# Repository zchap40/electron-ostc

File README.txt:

Acorn Electron Open Source Turbo Card
-------------------------------------

The Acorn Electron OSTC is a 'turbo card' that speeds up the Electron by partially 
mitigating the slow memory access that usually limits the 6502 CPU's performance. It 
acts similarly to ye olde turbo cards of days gone by, like the Slogger Turbo Driver, 
but is implemented using modern programmable logic and SRAM.

How it works
------------

Electrons are slow because of the ULA stealing RAM cycles to update the
display. When reading from the ROM the CPU works at 2MHz, but when accessing
RAM it runs at 1MHz in modes 4-6. In modes 0-3 the ULA stops the CPU clock
when drawing the display area, effectively throttling the 6502 down to 
around 0.5MHz.

Turbo cards are based on an interesting quirk; the ULA only needs to access
the upper 20K of system RAM for display purposes. The lower 12K is contended
between the ULA and CPU purely to simplify the Electron's design.

The trick is to stop the ULA from contending the lower 12K. We do this by
adding some new memory dedicated to the CPU, in this case a 32K SRAM chip.
All reads and writes to the 0-12K area are redirected to the SRAM chip - old
turbo cards handled the first 8K only to simplify the required logic, but here
we do all 12K. The 6502's databus is passed through the CPLD chip, which sets
it to high impedance when the SRAM is being accessed, effectively preventing
the Elk's on-board DRAM from causing bus contention.

That's great, but we're still not going any faster. The ULA is still throttling
the CPU clock, even when we're now accessing that lovely fast SRAM chip and not
the grotty contended motherboard DRAM.

The solution is to run the CPU's A15, A14 and RW lines through the CPLD. When
the CPU accesses the SRAM chip the CPLD pulls all of those lines high on the
ULA side, fooling it into thinking we are reading from the ROM - the the ULA
duly accelerates the CPU to 2MHz. The actual data read from the ROM never
reaches the CPU as the CPLD acts as a bus isolator at this point, cutting the CPU
and SRAM off from the motherboard.

One major difference between the older turbos and the OSTC is how 
disabling the board is handled. Other boards required a reboot after toggling
the board state. 

The OSTC never actually disables, the switch just returns the CPU to
normal speed. R/W operations are still processed by the SRAM chip, not DRAM.

This has the big advantage that SRAM contents is always up to date and turbo
speed can be toggled without a reboot. Downside is the very few games that try
to locate the display < 12K won't run.

Versions
--------

The OSTC was originally designed and developed by G. Colville (ramtop-retro).
OSTC_v1 can be downloaded from ramtop-retro/ostc.

Here we present a more compact version of the PCB, with an almost identical circuit,
filed here as OSTC_v2. The Electron is not just an elegant looking machine from
the exterior, but in my opinion, is also of elegant design on the inside too. I wanted
a version of the OSTC that matched the aesthetic of the Electron's motherboard without
being unnecessarily large, and for that you may find OSTC_v2 of interest.

The turbo switching functionality of the original OSTC circuit throttles the speed via
the turbo card itself, and does not actually physically switch the card out of the 
motherboard. OSTC_v3 takes the idea for the Electron OSTC further by providing actual hardware 
switching functionality. It employs high-bandwidth analog data switches to connect the 
12 re-routed data lines from the motherboard to either the OSTC circuit, or directly to 
the 6502 processor. This is controlled by the on-board three-way switch, allowing the turbo 
card to be set to 1) turbo speed, 2) normal speed (throttled), and 3) native speed (turbo card
physically switched out). Similarly, dual two-pin micro headers allow two separate external
switches to be connected in lieux of the on-board switch to disable turbo mode via 'native'
mode, where the turbo card is completely switched out of the hardware, or 'normal' mode,
through speed throttling by the turbo card itself. Of course, the Electron will always have
to be rebooted after switching between 'native' mode and the other two modes.

Although higher in cost and more difficult to construct, OSTC_v3 allows the Electron to
easily switch back to a state where it is completely unmodified without having to open up the
machine and physically remove the turbo card.

Files
-----

 - PCB 		PCB layout in Diptrace format for OSTC_v1, and Autodesk Eagle format
		for OSTC_v2 and v3
 - Gerbers	Gerber and drill files for OSTC_v1, v2 and v3
 - Schematics	PDF schematic diagrams for OSTC_v2 and v3
 - ISE		Xilinx ISE project (verilog)
 - CPLD		Programming file for the CPLD

How to build it
---------------

The 'Gerbers' directory contains Zip files for each version that you can upload to any 
PCB fabrication service to have them produce OSTC PCBs for you. In Europe, aisler.net
is recommended. Please note that all three versions of the PCB are 4-layer boards.

The 'PCB' directory has the original PCB layout files in Diptrace format for version 1,
and Autodesk Eagle format for versions 2 & 3. Many PCB fabrication houses (including
Aisler and OSHPark) allow you to upload the original PCB design files (.dip for Diptrace
and .brd for Eagle) instead of Zipped gerber files, and this in fact usually allows the
boards to be rendered even more accurately by the fabrication house. It is recommended
to go this route if this option is available.

**OSTC_v1**

The components necessary for OSTC_v1 are:

REF			Component 					Part No.

C1, C2, C3		150pF 1206 size ceramic capacitor		399-8157-1-ND (Digikey)
C4, C5			22uF 1206 size tantalum capacitor		478-3865-1-ND (Digikey)
VR3v3			3.3v LM1117 voltage regulator			LM1117MP-3.3/NOPBCT-ND (Digikey)
R1			2Kohm 1206 resistor				RMCF1206JT2K00CT-ND (Digikey)
R2			4Kohm 1206 resistor				RNCP1206FTD4K02CT-ND (Digikey)
JTAG, SW1, DBG		0.1" pin headers, right-angle			547-3223 (RS Components)
6502			2x Low profile 40-way turned pin socket 	197-2726 (RS Components)
ElkMB			2x 20 way round pin headers (see below)		BBL-120-T-E (Toby Electronics)
XC9500XL		Xilinx XC9536XL 44-pin VQFP			122-1385-ND (Digikey)
SRAM			IS62C256AL-45ULI 28-pin SOP			706-1043-ND (Digikey)

OSTC_v1 has been designed to be fairly easy to build if you have some surface mount
soldering experience. A few points to note, however:

- Capacitor and resistor values are not super critical, but C4/5 should be tantalums of
at least 22uF or stability may be affected.
- I strongly recommend using turned pin type sockets, these are much more reliable than
the dual-wipe type, but they absolutely require the round-pin type headers listed above
and not the cheaper, more common, square pin type.
- The JTAG header should be right-angle, with the pins located over the top of the CPLD.
- DBG is the debug header, fitting this is not required

CPU speed is controlled by pins 1 and 2 of SW1. Shorting these pins slows the CPU to stock
speed, open is turbo speed.

JTAG header pinout is :

1 3.3v
2 GND
3 TCK
4 TDO
5 TDI
6 TMS

**OSTC_v2**

The components necessary for OSTC_v2 are:

REF	QTY	Component 					Part No.

X1	1	Molex 505567-0651 6-ckt Micro-Lock socket	538-505567-0651 (Mouser)
X2	1	Molex 505567-0251 2-ckt Micro-Lock socket	538-505567-0251 (Mouser)
X3	2	Samtec BBL-120-G-E 20-way 0.1" terminal strip	200-BBL120GE (Mouser)
U1	1	Samtec ICO-640-CGG 40-DIP low-profile socket	200-ICO640LGG (Mouser)
U2	1	Xilinx XC9536XL-10CSG48I 48-BGA CPLD		217-C9536XL-10CSG48I (Mouser)
U3	1	ISSI IS62C256AL-45TLI 28-TSOP 8x32k SRAM	870-IS62C256AL-45TLI (Mouser)
U4	1	Texas LP5912Q3.3DRVRQ1 6-WSON 3.3V regulator	595-LP5912Q3.3DRVRQ1 (Mouser)
S1	1	NKK SS312SAH4 SPDT slide-switch			633-SS312SAH4 (Mouser)
C1, C2	2	10uF X7R ceramic capacitor, 1206 SMD		810-CGA5L1X7R1H106K6 (Mouser)
C3, C4	2	100nF X7R ceramic capacitor, 1206 SMD		810-CGA5L2X7R2A104K (Mouser)
R1	1	4K7 0.25W resistor, 0805 SMD			660-RK73H2ATTD4701F (Mouser)	

Cable	1	Molex 45111-0606 Micro-Lock cable		538-45111-0606 (Mouser)
		(for programming CPLD)
Cable	1	Molex 45111-0206 Micro-Lock cable		538-45111-0206 (Mouser)
		(for connecting external switch)

**OSTC_v3**

The components necessary for OSTC_v3 are:

REF	QTY	Component 					Part No.

X1	1	Molex 505567-0651 6-ckt Micro-Lock socket	538-505567-0651 (Mouser)
X2	2	Molex 505567-0251 2-ckt Micro-Lock socket	538-505567-0251 (Mouser)
X3	2	Samtec BBL-120-G-E 20-way 0.1" terminal strip	200-BBL120GE (Mouser)
U1	1	Samtec ICO-640-CGG 40-DIP micro-profile socket	200-ICO640CGG (Mouser)
U2	1	Xilinx XC9536XL-10CSG48I 48-BGA CPLD		217-C9536XL-10CSG48I (Mouser)
U3	1	ISSI IS62C256AL-45TLI 28-TSOP 8x32k SRAM	870-IS62C256AL-45TLI (Mouser)
U4	1	Texas LP5912Q3.3DRVRQ1 6-WSON 3.3V regulator	595-LP5912Q3.3DRVRQ1 (Mouser)
U5, U6	4	Maxim MAX4996ETG+ 24-TQFN 3x DPDT analog switch	700-MAX4996ETG (Mouser)
U7, U8	
S1	1	NKK SS314MAH4 SP3T slide-switch			633-SS314MAH4-R (Mouser)
C1, C2	2	10uF X7R ceramic capacitor, 0805 SMD		81-GRM21BZ71E106KE5K (Mouser)
C3, C4	2	100nF X7R ceramic capacitor, 0805 SMD		80-C0805X104J5RAUTO (Mouser)
R1, R2	2	4K7 0.25W resistor, 0805 SMD			660-RK73H2ATTD4701F (Mouser)

Cable	1	Molex 45111-0606 Micro-Lock cable		538-45111-0606 (Mouser)
		(for programming CPLD)
Cable	1	Molex 45111-0206 Micro-Lock cable		538-45111-0206 (Mouser)
		(for connecting external switch)

How to fit it
-------------

Fitting the OSTC requires the Electron's 6502 CPU to be desoldered from the motherboard. It
is strongly recommended you use a proper vacuum desoldering station to do this, or find
someone who can do it for you, as the Elk's PCB is quite fragile. It is recommended to install
the following low-profile machined-pin socket on the Electron motherboard:

Component 					Part No.
Samtec ICA-640-SGG				200-ICA640SGG (Mouser)

Once the CPU is removed it should be installed into the socket on the OSTC marked '6502' (marked 'U1'
on OSTC_v2 and v3) with the orientation notch facing away from the JTAG header. Then, solder the
recommended 40-pin socket into the CPU area (IC3) on the motherboard. Insert the OSTC into the socket,
pushing firmly and making sure it is correctly aligned.

If you want to externally control the CPU speed, a switch can be connected between pins 1 and 2 of
SW1 on OSTC_v1. On OSTC_v2, the same function is served via a Molex Micro-Lock cable assembly that can be
attached to the 2-pin Micro-Lock header (X2). On OSTC_v3, the same Molex Micro-Lock connector controls
hardware switch-in/out of the turbo card, instead of speed throttling by the turbo card.

A Rockwell R65C02 rated 2MHz or faster can be fitted in place of the original NMOS 6502, to
reduce heat build-up. WDC branded 65C02s will not work.

License
-------
Copyright for all the files in this repository copied from ramtop-retro/ostc remains with G. Colville, but
can be freely used for non-commercial purposes.

Copyright for all other files remains with A. Sadek, and may be used similarly.

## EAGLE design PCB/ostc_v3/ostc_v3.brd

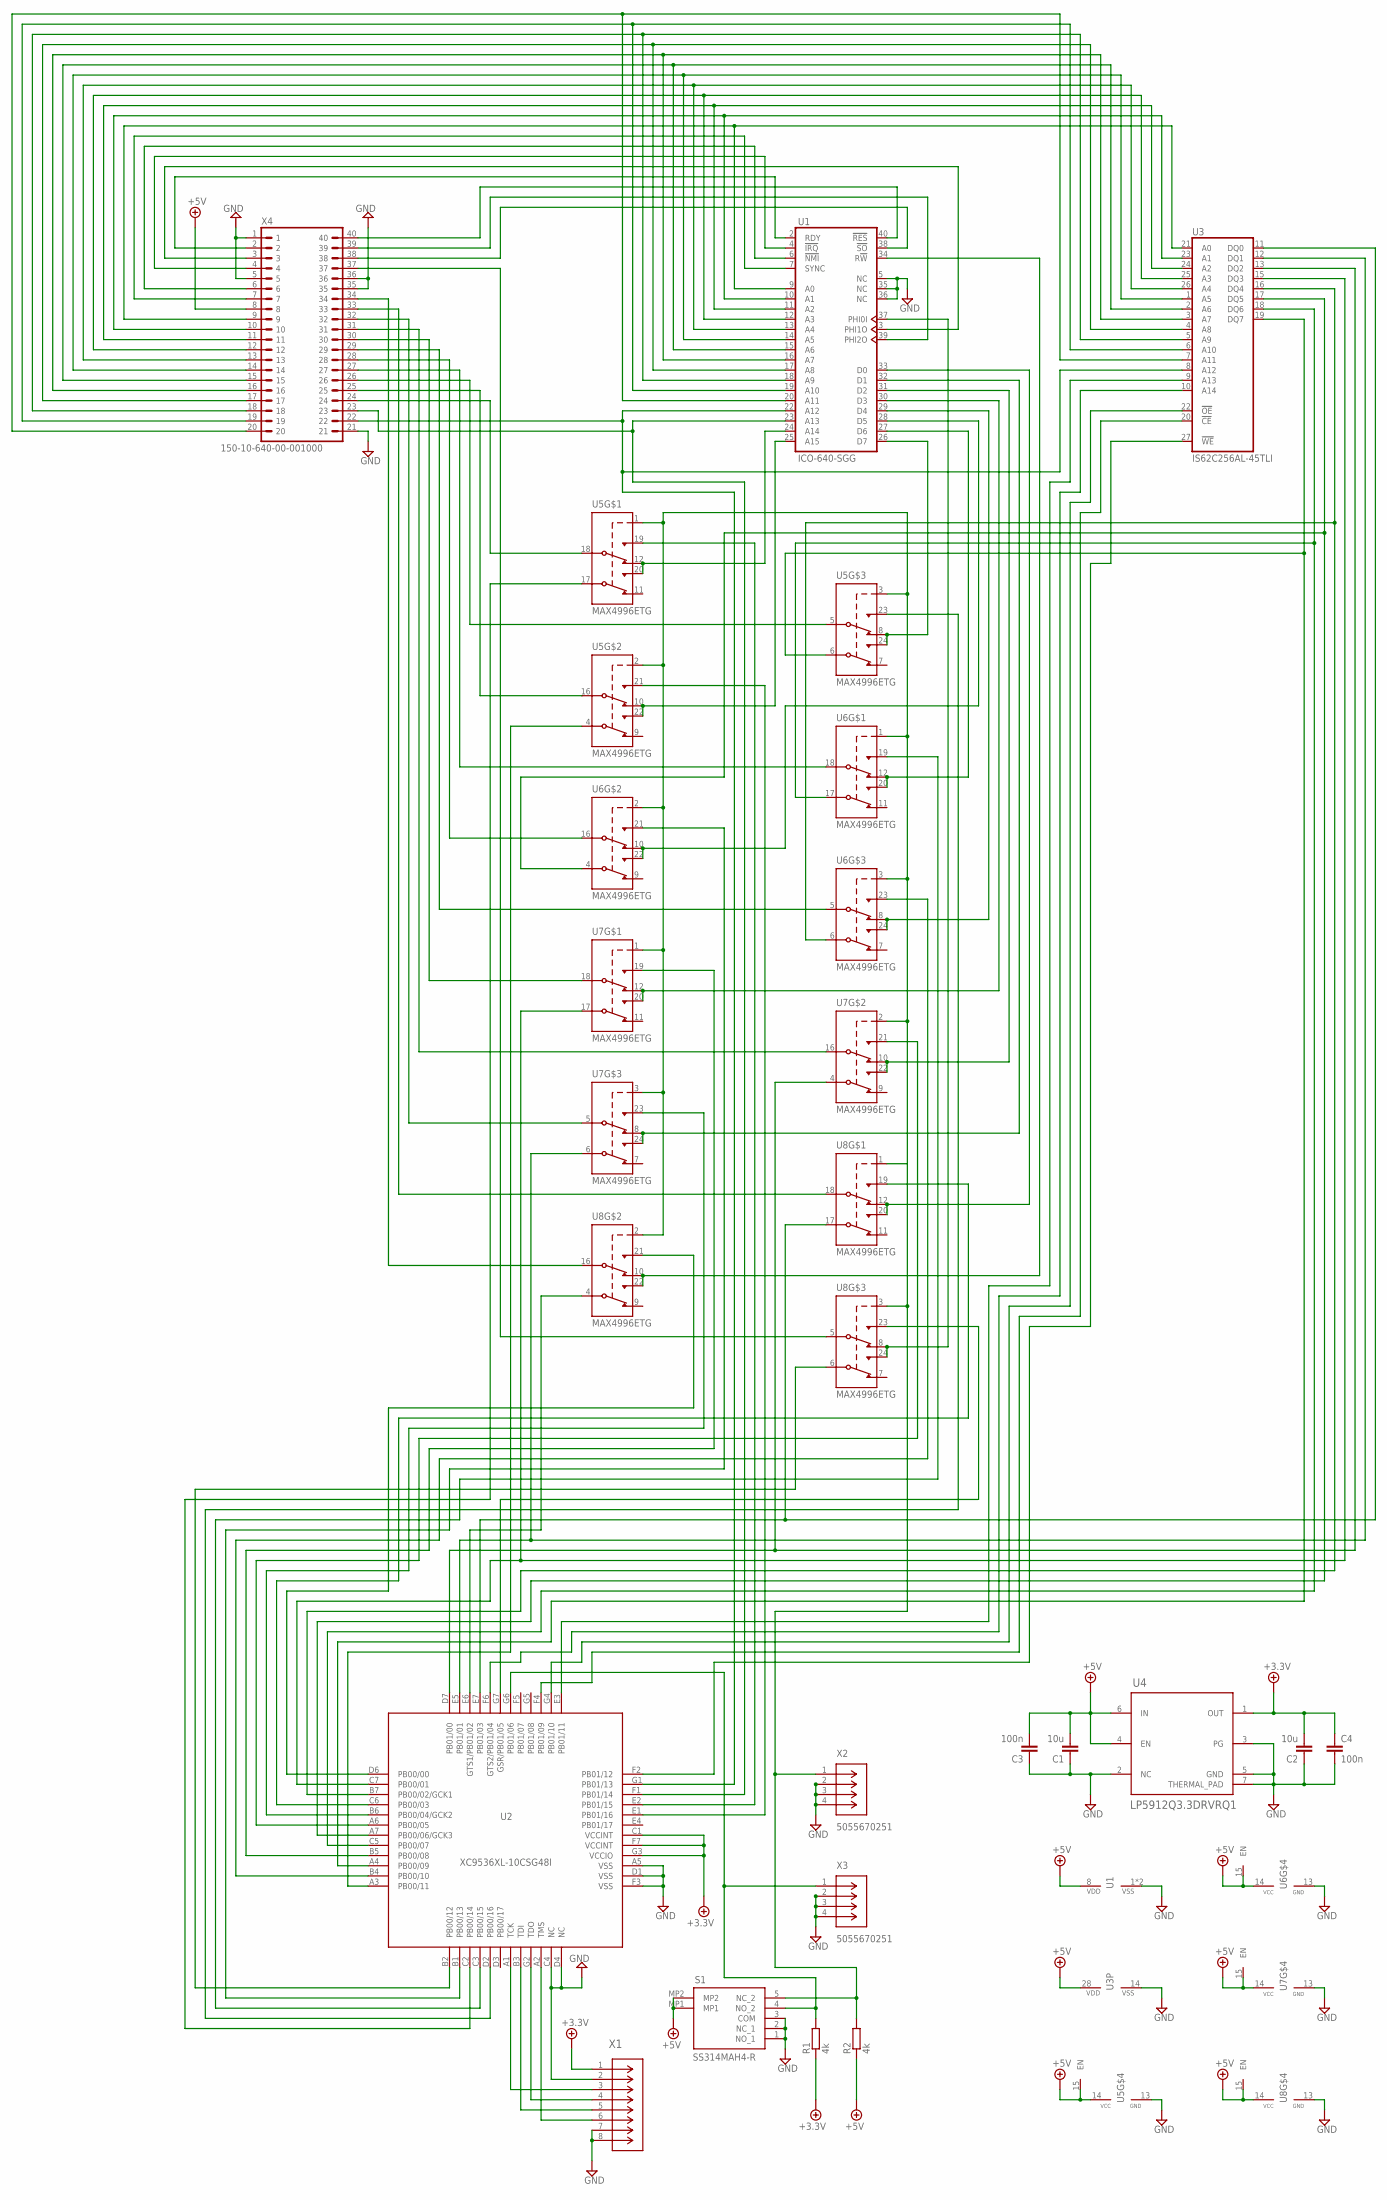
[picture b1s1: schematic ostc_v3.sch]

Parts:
C1, C2: 10u; C0805
C3, C4: 100n; C0805
R1, R2: 4k; R0805
S1: SS314MAH4-R; SS314MAH4R
U1: ICO-640-SGG; DIL40_MICROPROFILE
U2: XC9536XL-10CSG48I; CSBGA48
U3: IS62C256AL-45TLI; TSOP1-28
U4: LP5912Q3.3DRVRQ1; DRV0006A-IPC_A
U5, U6, U7, U8: MAX4996ETG; TQFN24
X1: 505567-0651; CON_5055670651
X2, X3: 5055670251; CON_5055670251
X4: 150-10-640-00-001000; DIL40

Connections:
+3.3V: C2.2, C4.1, R1.1, U2.C1 (VCCINT), U2.F7 (VCCINT), U2.G3 (VCCIO), U4.1 (OUT), X1.1
+5V: C1.2, C3.2, R2.1, S1.MP1, S1.MP2, U1.8 (VDD), U3.28 (VDD), U4.4 (EN), U4.6 (IN), U5.14 (VCC), U5.15 (EN), U6.14 (VCC), U6.15 (EN), U7.14 (VCC), U7.15 (EN), U8.14 (VCC), U8.15 (EN), X4.8
GND: C1.1, C2.1, C3.1, C4.2, S1.1 (NO_1), S1.2 (NC_1), S1.3 (COM), U1.1 (VSS), U1.5 (NC), U1.21 (VSS), U1.35 (NC), U1.36 (NC), U2.A5 (VSS), U2.C4 (NC), U2.D1 (VSS), U2.D4 (NC), U2.F3 (VSS), U3.14 (VSS), U4.2 (NC), U4.3 (PG), U4.5 (GND), U4.7 (THERMAL_PAD), U5.13 (GND), U6.13 (GND), U7.13 (GND), U8.13 (GND), X1.2, X1.7, X1.8, X2.2, X2.3, X2.4, X3.2, X3.3, X3.4, X4.1, X4.5, X4.21, X4.35, X4.36
unnamed: U1.2 (RDY), X4.2
unnamed: U1.3 (PHI1O), X4.3
unnamed: U1.4 (!IRQ), X4.4
unnamed: U1.6 (!NMI), X4.6
unnamed: U1.7 (SYNC), X4.7
unnamed: U1.9 (A0), U3.21 (A0), X4.9
unnamed: U1.10 (A1), U3.23 (A1), X4.10
unnamed: U1.11 (A2), U3.24 (A2), X4.11
unnamed: U1.12 (A3), U3.25 (A3), X4.12
unnamed: U1.13 (A4), U3.26 (A4), X4.13
unnamed: U1.14 (A5), U3.1 (A5), X4.14
unnamed: U1.15 (A6), U3.2 (A6), X4.15
unnamed: U1.16 (A7), U3.3 (A7), X4.16
unnamed: U1.17 (A8), U3.4 (A8), X4.17
unnamed: U1.18 (A9), U3.5 (A9), X4.18
unnamed: U1.19 (A10), U3.6 (A10), X4.19
unnamed: U1.20 (A11), U3.7 (A11), X4.20
unnamed: U2.E2 (PB01/15), U5.19 (NO1)
unnamed: U1.22 (A12), U2.G1 (PB01/13), U3.8 (A12), X4.22
unnamed: U1.23 (A13), U2.F1 (PB01/14), X4.23
unnamed: U2.E1 (PB01/16), U5.21 (NO1)
unnamed: U2.D2 (PB00/16), U5.23 (NO1)
unnamed: U2.C3 (PB00/15), U6.19 (NO1)
unnamed: U2.B1 (PB00/13), U6.21 (NO1)
unnamed: U2.B4 (PB00/10), U6.23 (NO1)
unnamed: U2.B5 (PB00/08), U7.19 (NO1)
unnamed: U2.A6 (PB00/05), U7.21 (NO1)
unnamed: U2.B6 (PB00/04/GCK2), U7.23 (NO1)
unnamed: U2.C6 (PB00/03), U8.19 (NO1)
unnamed: U2.D6 (PB00/00), U8.21 (NO1)
unnamed: U8.5 (COM1), X4.37
unnamed: U1.38 (!SO), X4.38
unnamed: U1.39 (PHI2O), X4.39
unnamed: U1.40 (!RES), X4.40
unnamed: U2.B2 (PB00/12), U8.6 (COM2)
unnamed: U2.E6 (GTS1/PB01/02), U8.4 (COM2)
unnamed: U2.E7 (PB01/03), U3.11 (DQ0), U8.17 (COM2)
unnamed: U2.E5 (PB01/01), U3.12 (DQ1), U7.6 (COM2)
unnamed: U2.D7 (PB01/00), U3.13 (DQ2), U7.4 (COM2)
unnamed: U2.C7 (PB00/01), U3.15 (DQ3), U7.17 (COM2)
unnamed: U2.B7 (PB00/02/GCK1), U3.16 (DQ4), U6.6 (COM2)
unnamed: U2.A7 (PB00/06/GCK3), U3.17 (DQ5), U6.4 (COM2)
unnamed: U2.C5 (PB00/07), U3.18 (DQ6), U6.17 (COM2)
unnamed: U2.A4 (PB00/09), U3.19 (DQ7), U5.6 (COM2)
unnamed: R1.2, S1.4 (NO_2), U2.G6 (PB01/06), X3.1
unnamed: U1.24 (A14), U5.12 (NC1), U5.20 (NO2)
unnamed: U1.26 (D7), U5.8 (NC1), U5.24 (NO2)
unnamed: U5.16 (COM1), X4.25
unnamed: U1.25 (A15), U5.10 (NC1), U5.22 (NO2)
unnamed: U5.5 (COM1), X4.26
unnamed: R2.2, S1.5 (NC_2), U5.1 (CB), U5.2 (CB), U5.3 (CB), U6.1 (CB), U6.2 (CB), U6.3 (CB), U7.1 (CB), U7.2 (CB), U7.3 (CB), U8.1 (CB), U8.2 (CB), U8.3 (CB), X2.1
unnamed: U6.18 (COM1), X4.27
unnamed: U2.A3 (PB00/11), U5.4 (COM2)
unnamed: U2.C2 (PB00/14), U5.17 (COM2)
unnamed: U2.A2 (TMS), X1.6
unnamed: U2.B3 (TDI), X1.5
unnamed: U2.G2 (TDO), X1.4
unnamed: U2.A1 (TCK), X1.3
unnamed: U1.27 (D6), U6.12 (NC1), U6.20 (NO2)
unnamed: U5.18 (COM1), X4.24
unnamed: U6.16 (COM1), X4.28
unnamed: U1.28 (D5), U6.10 (NC1), U6.22 (NO2)
unnamed: U7.16 (COM1), X4.31
unnamed: U1.29 (D4), U6.8 (NC1), U6.24 (NO2)
unnamed: U6.5 (COM1), X4.29
unnamed: U7.18 (COM1), X4.30
unnamed: U1.30 (D3), U7.12 (NC1), U7.20 (NO2)
unnamed: U1.31 (D2), U7.10 (NC1), U7.22 (NO2)
unnamed: U7.5 (COM1), X4.32
unnamed: U1.32 (D1), U7.8 (NC1), U7.24 (NO2)
unnamed: U1.33 (D0), U8.12 (NC1), U8.20 (NO2)
unnamed: U8.18 (COM1), X4.33
unnamed: U8.16 (COM1), X4.34
unnamed: U1.34 (R!W), U8.10 (NC1), U8.22 (NO2)
unnamed: U1.37 (PHI0I), U8.8 (NC1), U8.24 (NO2)
unnamed: U2.G7 (GSR/PB01/05), U8.23 (NO1)
unnamed: U2.E3 (PB01/11), U3.9 (A13)
unnamed: U2.F6 (GTS2/PB01/04), U3.10 (A14)
unnamed: U2.G4 (PB01/10), U3.22 (!OE)
unnamed: U2.F4 (PB01/09), U3.20 (!CE)
unnamed: U2.F2 (PB01/12), U3.27 (!WE)

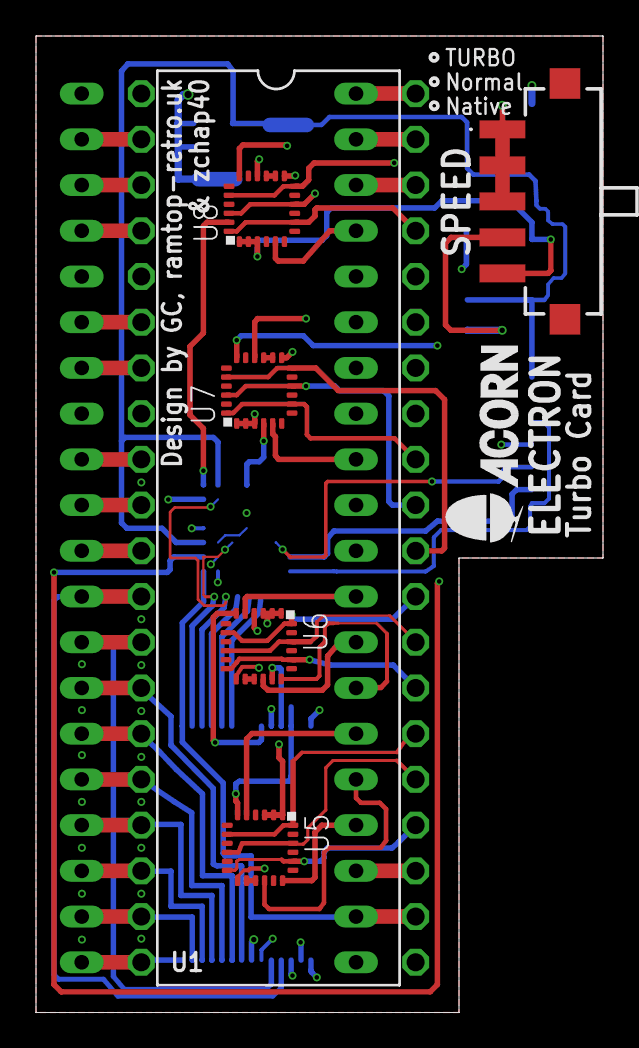
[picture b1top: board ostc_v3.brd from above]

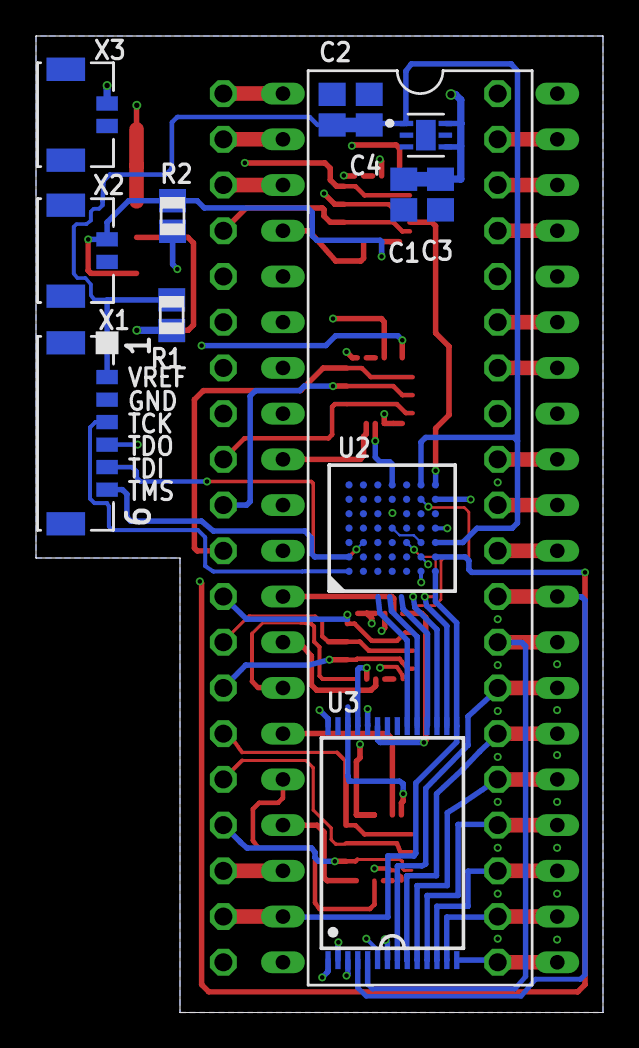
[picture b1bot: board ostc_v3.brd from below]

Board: 4 copper layers, 31.5 x 54.2 mm, 19 parts (12 on the bottom side), 84 nets.

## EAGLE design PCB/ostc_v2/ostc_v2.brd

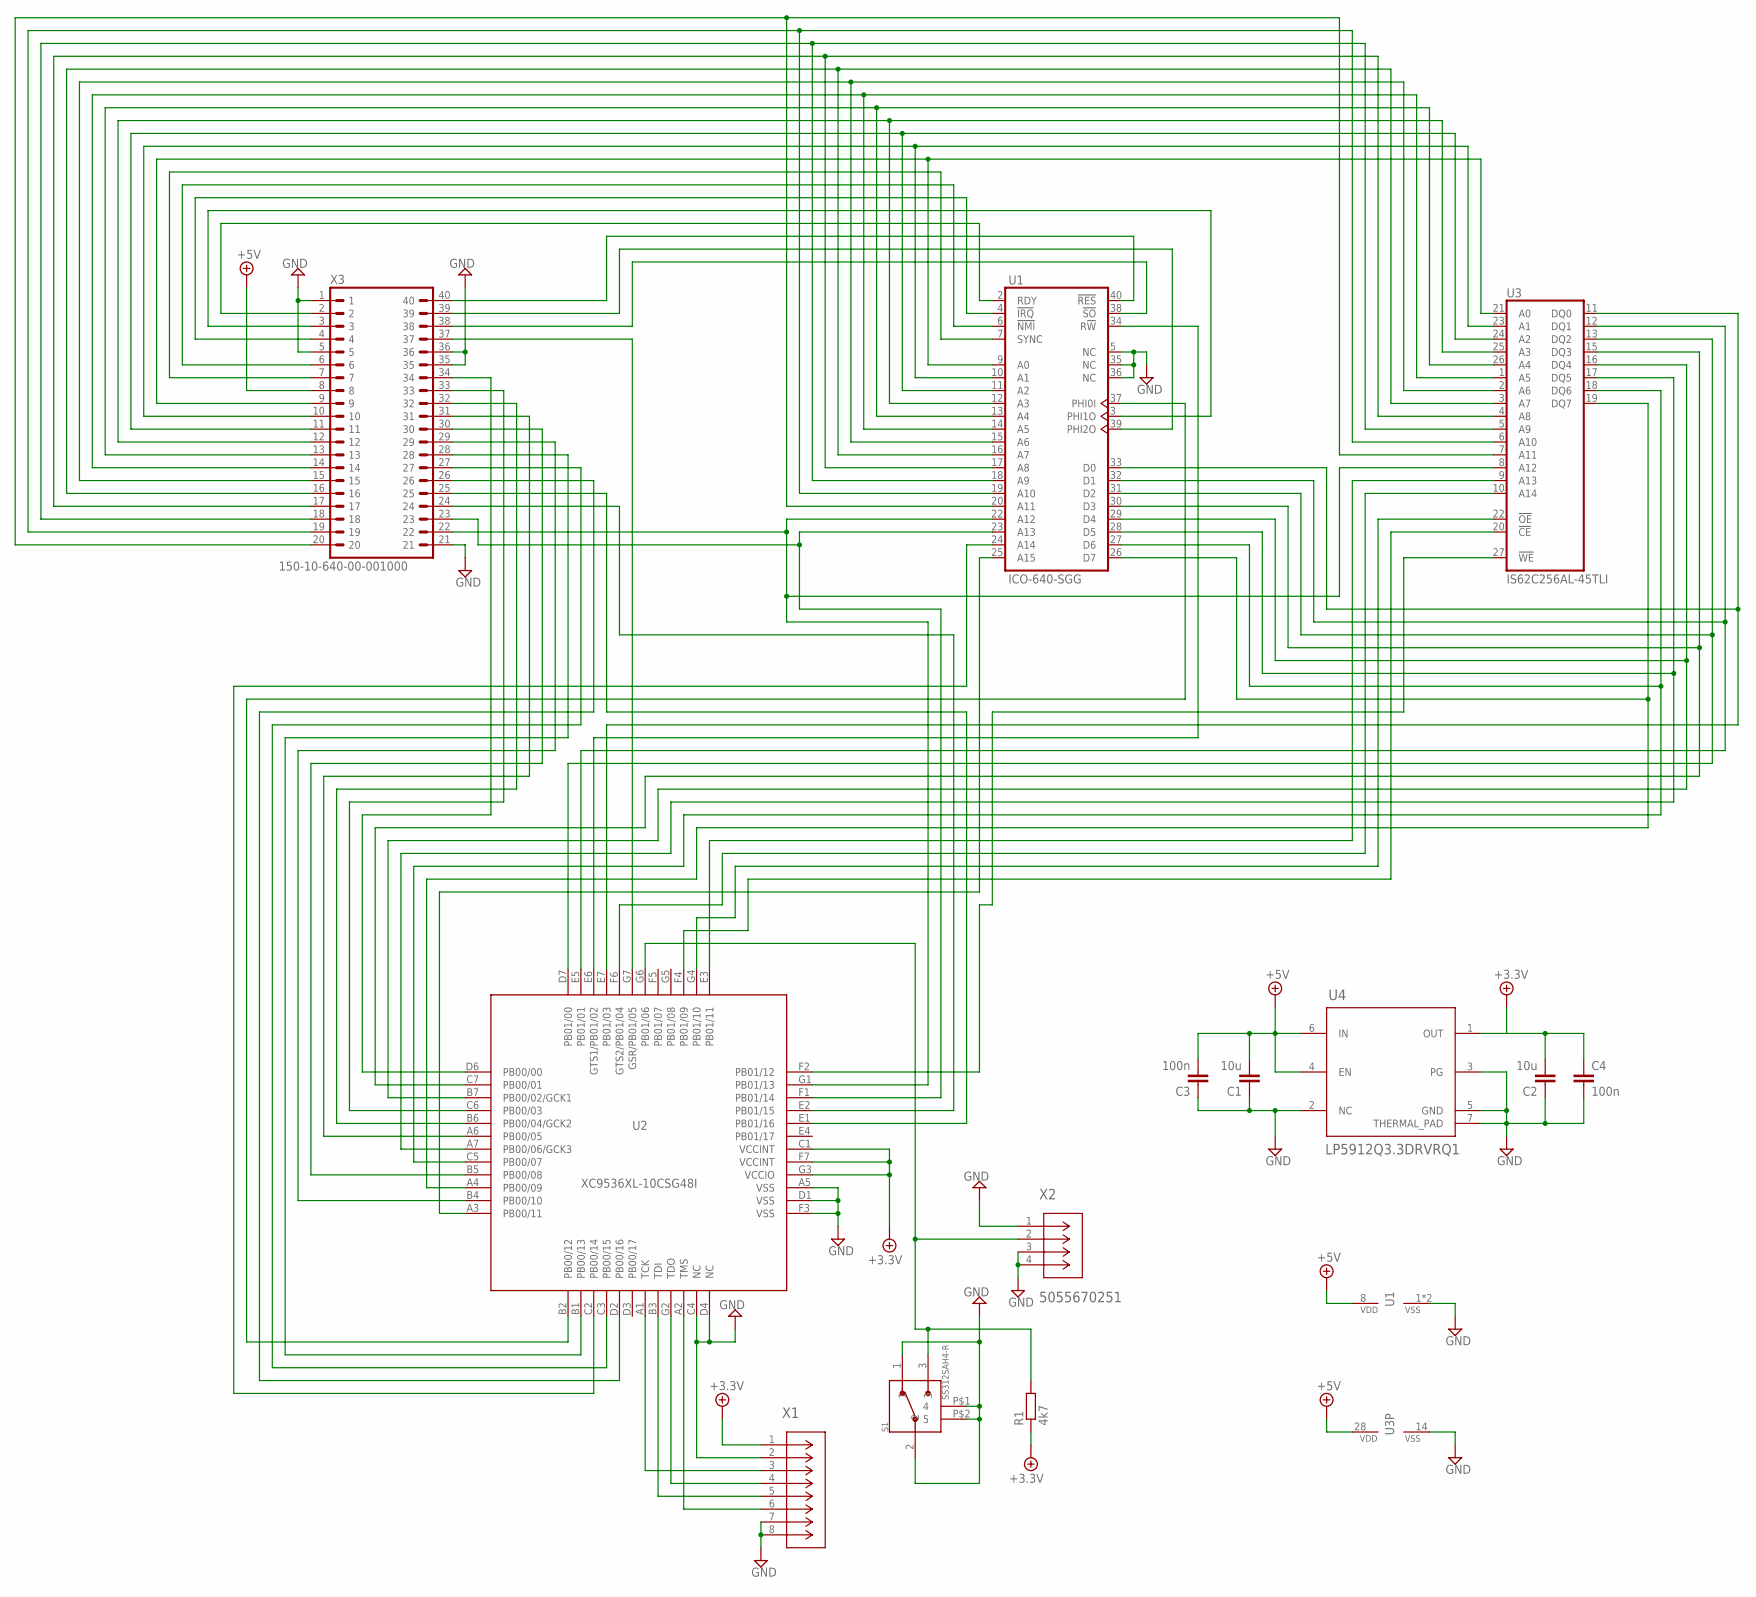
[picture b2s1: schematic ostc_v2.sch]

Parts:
C1, C2: 10u; C1206K
C3, C4: 100n; C1206K
R1: 4k7; R0805
S1: SS312SAH4-R; SW_SS312SAH4-R
U1: ICO-640-SGG; DIL40_LOWPROFILE
U2: XC9536XL-10CSG48I; CSBGA48
U3: IS62C256AL-45TLI; TSOP1-28
U4: LP5912Q3.3DRVRQ1; DRV0006A-IPC_A
X1: 5055670651; CON_5055670651
X2: 5055670251; CON_5055670251
X3: 150-10-640-00-001000; DIL40

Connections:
+3.3V: C2.2, C4.1, R1.1, U2.C1 (VCCINT), U2.F7 (VCCINT), U2.G3 (VCCIO), U4.1 (OUT), X1.1
+5V: C1.2, C3.2, U1.8 (VDD), U3.28 (VDD), U4.4 (EN), U4.6 (IN), X3.8
GND: C1.1, C2.1, C3.1, C4.2, S1.1, S1.2, S1.P$1 (4), S1.P$2 (5), U1.1 (VSS), U1.5 (NC), U1.21 (VSS), U1.35 (NC), U1.36 (NC), U2.A5 (VSS), U2.C4 (NC), U2.D1 (VSS), U2.D4 (NC), U2.F3 (VSS), U3.14 (VSS), U4.2 (NC), U4.3 (PG), U4.5 (GND), U4.7 (THERMAL_PAD), X1.2, X1.7, X1.8, X2.1, X2.3, X2.4, X3.1, X3.5, X3.21, X3.35, X3.36
unnamed: U1.2 (RDY), X3.2
unnamed: U1.3 (PHI1O), X3.3
unnamed: U1.4 (!IRQ), X3.4
unnamed: U1.6 (!NMI), X3.6
unnamed: U1.7 (SYNC), X3.7
unnamed: U1.9 (A0), U3.21 (A0), X3.9
unnamed: U1.10 (A1), U3.23 (A1), X3.10
unnamed: U1.11 (A2), U3.24 (A2), X3.11
unnamed: U1.12 (A3), U3.25 (A3), X3.12
unnamed: U1.13 (A4), U3.26 (A4), X3.13
unnamed: U1.14 (A5), U3.1 (A5), X3.14
unnamed: U1.15 (A6), U3.2 (A6), X3.15
unnamed: U1.16 (A7), U3.3 (A7), X3.16
unnamed: U1.17 (A8), U3.4 (A8), X3.17
unnamed: U1.18 (A9), U3.5 (A9), X3.18
unnamed: U1.19 (A10), U3.6 (A10), X3.19
unnamed: U1.20 (A11), U3.7 (A11), X3.20
unnamed: U2.E2 (PB01/15), X3.24
unnamed: U1.22 (A12), U2.G1 (PB01/13), U3.8 (A12), X3.22
unnamed: U1.23 (A13), U2.F1 (PB01/14), X3.23
unnamed: U2.E1 (PB01/16), X3.25
unnamed: U2.D2 (PB00/16), X3.26
unnamed: U2.C3 (PB00/15), X3.27
unnamed: U2.B1 (PB00/13), X3.28
unnamed: U2.B4 (PB00/10), X3.29
unnamed: U2.B5 (PB00/08), X3.30
unnamed: U2.A6 (PB00/05), X3.31
unnamed: U2.B6 (PB00/04/GCK2), X3.32
unnamed: U2.C6 (PB00/03), X3.33
unnamed: U2.D6 (PB00/00), X3.34
unnamed: U2.G7 (GSR/PB01/05), X3.37
unnamed: U1.38 (!SO), X3.38
unnamed: U1.39 (PHI2O), X3.39
unnamed: U1.40 (!RES), X3.40
unnamed: U1.37 (PHI0I), U2.B2 (PB00/12)
unnamed: U1.34 (R!W), U2.E6 (GTS1/PB01/02)
unnamed: U1.33 (D0), U2.E7 (PB01/03), U3.11 (DQ0)
unnamed: U1.32 (D1), U2.E5 (PB01/01), U3.12 (DQ1)
unnamed: U1.31 (D2), U2.D7 (PB01/00), U3.13 (DQ2)
unnamed: U1.30 (D3), U2.C7 (PB00/01), U3.15 (DQ3)
unnamed: U1.29 (D4), U2.B7 (PB00/02/GCK1), U3.16 (DQ4)
unnamed: U1.28 (D5), U2.A7 (PB00/06/GCK3), U3.17 (DQ5)
unnamed: U1.27 (D6), U2.C5 (PB00/07), U3.18 (DQ6)
unnamed: U1.26 (D7), U2.A4 (PB00/09), U3.19 (DQ7)
unnamed: R1.2, S1.3, U2.G6 (PB01/06), X2.2
unnamed: U2.E3 (PB01/11), U3.9 (A13)
unnamed: U2.F6 (GTS2/PB01/04), U3.10 (A14)
unnamed: U2.G4 (PB01/10), U3.22 (!OE)
unnamed: U2.F4 (PB01/09), U3.20 (!CE)
unnamed: U2.F2 (PB01/12), U3.27 (!WE)
unnamed: U1.25 (A15), U2.A3 (PB00/11)
unnamed: U1.24 (A14), U2.C2 (PB00/14)
unnamed: U2.A2 (TMS), X1.6
unnamed: U2.B3 (TDI), X1.5
unnamed: U2.G2 (TDO), X1.4
unnamed: U2.A1 (TCK), X1.3

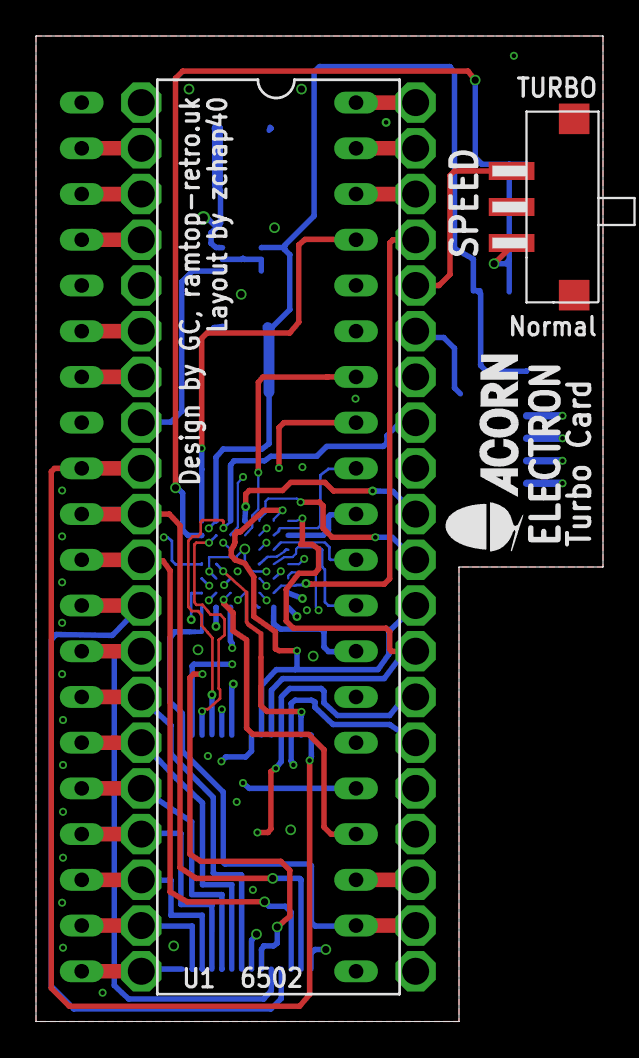
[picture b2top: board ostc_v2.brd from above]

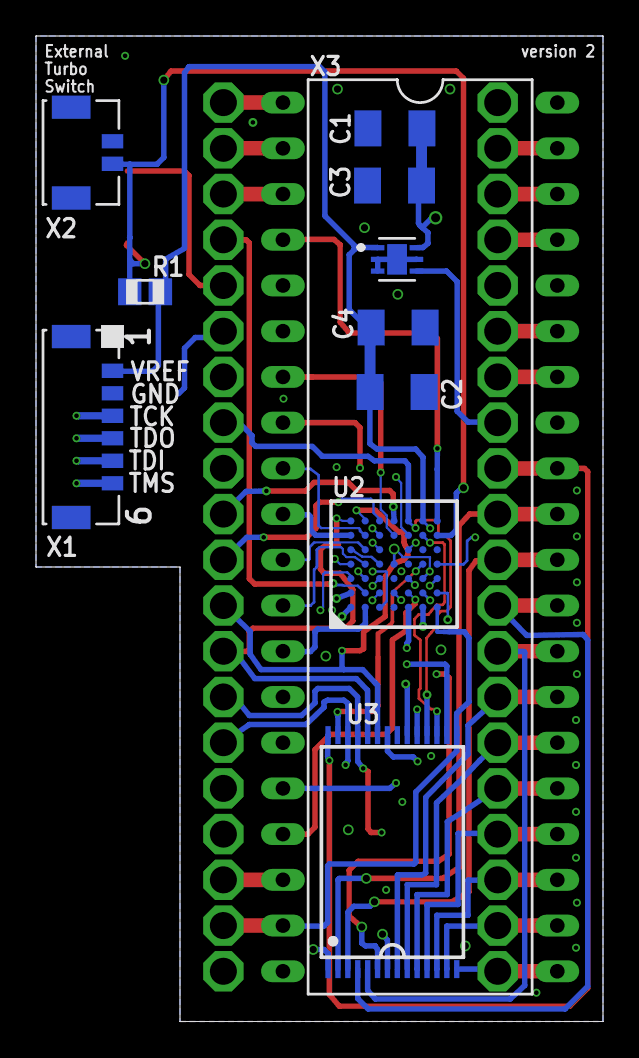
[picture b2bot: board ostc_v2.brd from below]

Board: 4 copper layers, 31.5 x 54.8 mm, 13 parts (10 on the bottom side), 59 nets.

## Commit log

2024-05-08 Gerbers
2024-05-08 Schematics
2024-05-09 . Please enter the commit message for your changes. Lines starting
    Updated README file
2024-05-13 Added version 3 schematics Added version 3 schematics
2024-05-13 Added Eagle schematic file for version 3
2024-05-13 Corrected schematic#
2024-05-13 Corrected schematic
2024-05-13 README.txt
2024-05-13 Modified schematics & boards
2024-05-13 Corrected schematics
2024-05-14 Updated PCB files
2024-05-14 Updated schematics
2024-05-14 Updated PCB
2024-05-15 Updated Gerbers
2024-05-15 Corrected PCB
2024-05-15 Corrected gerbers
2024-05-20 Added 3D files
2024-05-20 Updated 3D PCB files
2024-05-20 Updated 3D models
2024-05-21 Updated 3D renders
2024-05-21 Images and 3D renders
2024-05-21 Images and 3D renders of PCBs
2024-05-23 Updated PCB for tented vias
2024-05-23 Updated gerbers to include tented vias
2024-05-26 Updated PCBs, schematics, renders & gerbers
2024-05-26 Updated PCBs, gerbers & renders
2024-05-27 Updated PCBs, schematics, gerbers & renders
2024-06-01 Updated v3 brd - still incomplete
2024-06-03 Updated v3 PCB

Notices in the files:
parts and their libraries:
COPYRIGHT: Copyright (C) 2024 Ultra Librarian. All rights reserved.
